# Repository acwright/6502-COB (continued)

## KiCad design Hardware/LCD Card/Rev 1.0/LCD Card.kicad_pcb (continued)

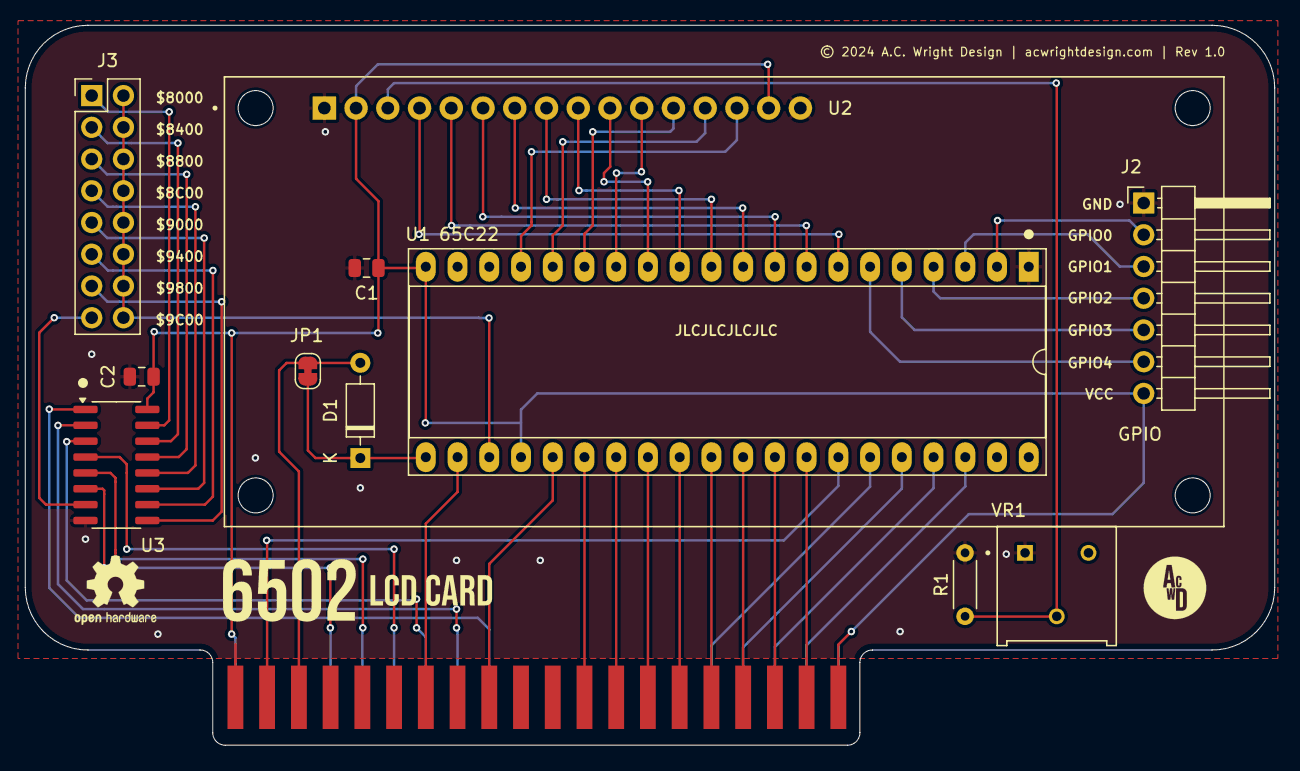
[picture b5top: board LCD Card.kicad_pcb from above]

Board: 2 copper layers, 100.0 x 57.6 mm, 12 parts (0 on the bottom side), 51 nets.
